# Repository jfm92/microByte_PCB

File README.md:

This repository contains the schematics and the PCB design of the microByte project with **KiCad 5.1.6.**

The 3D model of the components were obtained from [SnapEDA](https://www.snapeda.com/).

**If you want to know more about the microByte project go to the next link:**
[Github microByte](https://github.com/jfm92/microByte)

## 3D PCB Images

### PCB Front View

### PCB Bottom View

Note: Some of the compenent 3D models weren't available, thats the reason why they don't appear on the PCB.

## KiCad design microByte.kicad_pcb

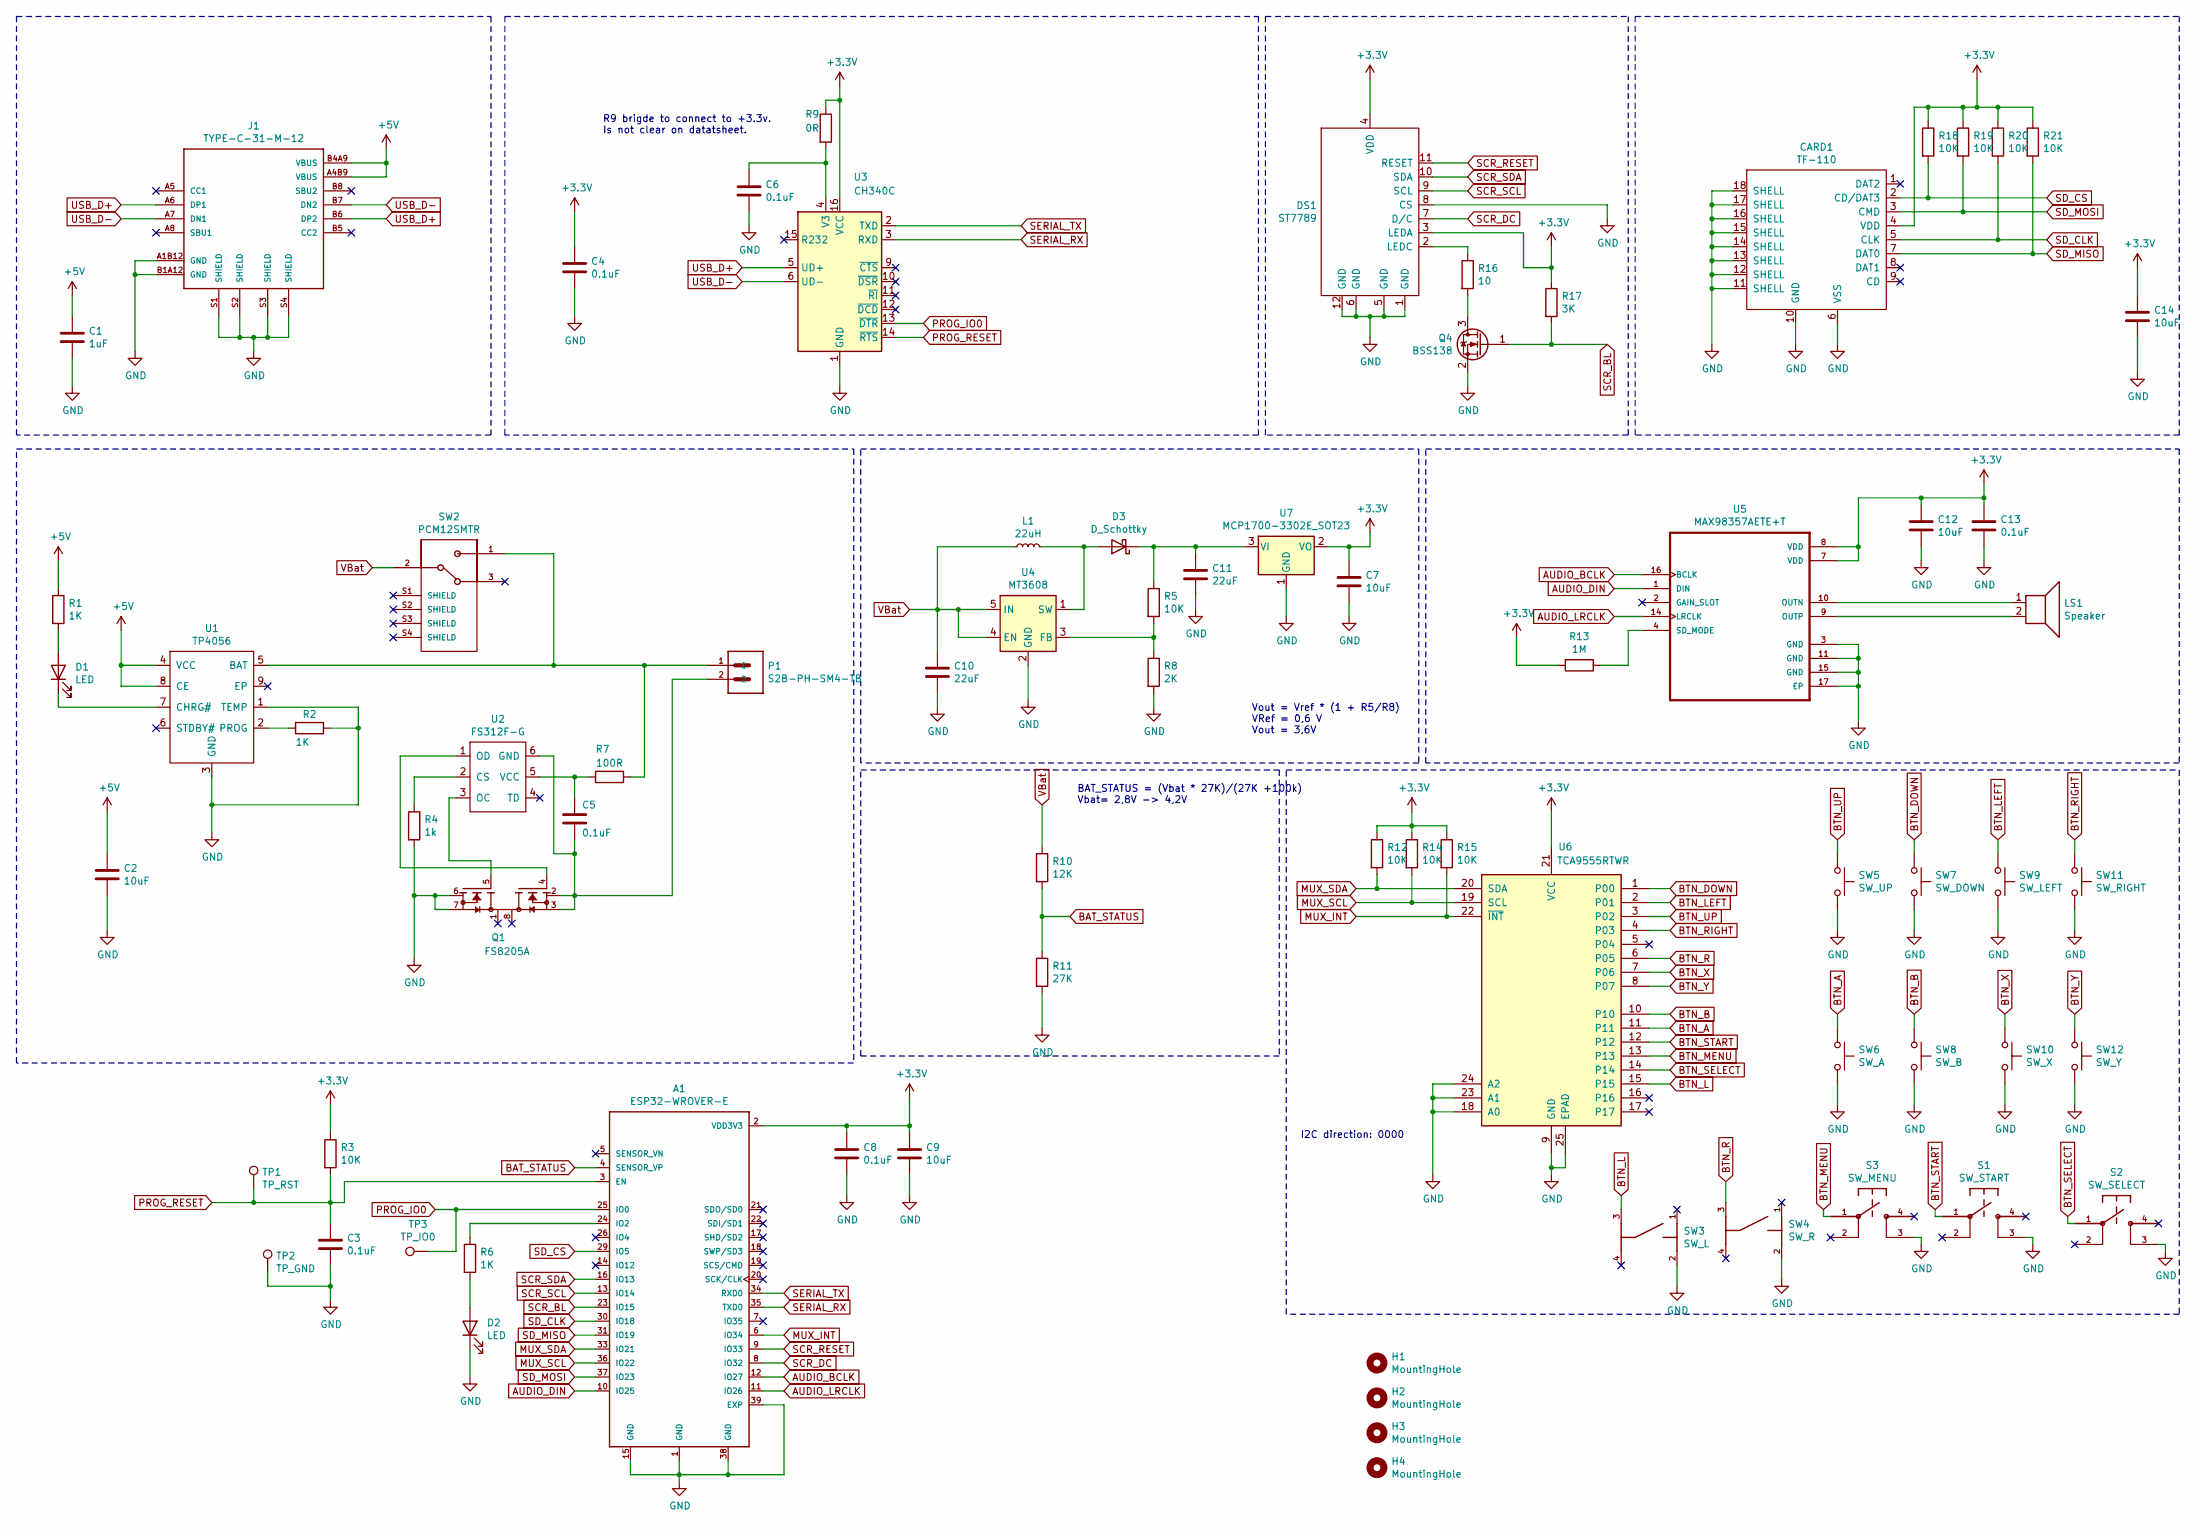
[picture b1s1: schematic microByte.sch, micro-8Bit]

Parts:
A1: ESP32-WROVER-E; XCVR_ESP32-WROVER-I
C1: 1uF; C_0805_2012Metric_Pad1.15x1.40mm_HandSolder
C2, C9, C12, C14: 10uF; C_0805_2012Metric_Pad1.15x1.40mm_HandSolder
C3, C4, C5, C6, C8, C13: 0.1uF; C_0603_1608Metric_Pad1.05x0.95mm_HandSolder
C7: 10uF; C_0805_2012Metric
C10, C11: 22uF; C_0805_2012Metric_Pad1.15x1.40mm_HandSolder
CARD1: TF-110
D1, D2: LED; LED_0805_2012Metric_Pad1.15x1.40mm_HandSolder
D3: D_Schottky; D_SMA_Handsoldering
DS1: ST7789
H1, H2, H3, H4: MountingHole; MountingHole_2.5mm
J1: TYPE-C-31-M-12; HRO_TYPE-C-31-M-12
L1: 22uH; Sunlord_SPH4012H220MT
LS1: Speaker; KLJ-5030
P1: S2B-PH-SM4-TB; JST_S2B-PH-SM4-TB
Q1: FS8205A; SOP65P640X120-8N
Q4: BSS138; SOT-23
R1, R2, R6: 1K; R_0805_2012Metric_Pad1.15x1.40mm_HandSolder
R3, R5, R12, R14, R15, R18, R19, R20, R21: 10K; R_0805_2012Metric_Pad1.15x1.40mm_HandSolder
R4: 1k; R_0805_2012Metric_Pad1.15x1.40mm_HandSolder
R7: 100R; R_0805_2012Metric_Pad1.15x1.40mm_HandSolder
R8: 2K; R_0805_2012Metric_Pad1.15x1.40mm_HandSolder
R9: 0R; R_0603_1608Metric_Pad1.05x0.95mm_HandSolder
R10: 12K; R_0805_2012Metric_Pad1.15x1.40mm_HandSolder
R11: 27K; R_0805_2012Metric_Pad1.15x1.40mm_HandSolder
R13: 1M; R_0805_2012Metric_Pad1.15x1.40mm_HandSolder
R16: 10; R_0805_2012Metric_Pad1.15x1.40mm_HandSolder
R17: 3K; R_0805_2012Metric_Pad1.15x1.40mm_HandSolder
S1: SW_START; TL3315NF100Q
S2: SW_SELECT; TL3315NF100Q
S3: SW_MENU; TL3315NF100Q
SW2: PCM12SMTR; SW_PCM12SMTR
SW3: SW_L; SW_434331013822
SW4: SW_R; SW_434331013822
SW5: SW_UP; BUTTON-CONDUCTIVE
SW6: SW_A; BUTTON-CONDUCTIVE
SW7: SW_DOWN; BUTTON-CONDUCTIVE
SW8: SW_B; BUTTON-CONDUCTIVE
SW9: SW_LEFT; BUTTON-CONDUCTIVE
SW10: SW_X; BUTTON-CONDUCTIVE
SW11: SW_RIGHT; BUTTON-CONDUCTIVE
SW12: SW_Y; BUTTON-CONDUCTIVE
TP1: TP_RST; TestPoint_Pad_D1.5mm
TP2: TP_GND; TestPoint_Pad_D1.5mm
TP3: TP_IO0; TestPoint_Pad_D1.5mm
U1: TP4056
U2: FS312F-G; SOT-23-6_Handsoldering
U3: CH340C; SOIC-16_3.9x9.9mm_P1.27mm
U4: MT3608; SOT-23-6
U5: MAX98357AETE+T; QFN50P300X300X80-17N
U6: TCA9555RTWR
U7: MCP1700-3302E_SOT23; SOT-23

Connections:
+3V3: A1.2 (VDD3V3), C4.1, C7.1, C8.1, C9.1, C12.1, C13.1, C14.1, CARD1.4 (VDD), DS1.3 (LEDA), DS1.4 (VDD), R3.1, R9.1, R12.1, R13.2, R14.1, R15.1, R17.1, R18.1, R19.1, R20.1, R21.1, U3.16 (VCC), U5.7 (VDD), U5.8 (VDD), U6.21 (VCC), U7.2 (VO)
+5V: C1.1, C2.1, J1.A4B9 (VBUS), J1.B4A9 (VBUS), R1.1, U1.4 (VCC), U1.8 (CE)
AUDIO_BCLK: A1.12 (IO27), U5.16 (BCLK)
AUDIO_DIN: A1.10 (IO25), U5.1 (DIN)
AUDIO_LRCLK: A1.11 (IO26), U5.14 (LRCLK)
BAT_STATUS: A1.4 (SENSOR_VP), R10.2, R11.1
BTN_A: SW6.1, U6.11
BTN_B: SW8.1, U6.10
BTN_DOWN: SW7.1, U6.1 (P00)
BTN_L: SW3.3, U6.15
BTN_LEFT: SW9.1, U6.2 (P01)
BTN_MENU: S3.1, U6.13
BTN_R: SW4.3, U6.6 (P05)
BTN_RIGHT: SW11.1, U6.4 (P03)
BTN_SELECT: S2.1, U6.14
BTN_START: S1.1, U6.12
BTN_UP: SW5.1, U6.3 (P02)
BTN_X: SW10.1, U6.7 (P06)
BTN_Y: SW12.1, U6.8 (P07)
GND: A1.1 (GND), A1.15 (GND), A1.38 (GND), A1.39 (EXP), C1.2, C2.2, C3.2, C4.2, C6.2, C7.2, C8.2, C9.2, C10.2, C11.2, C12.2, C13.2, C14.2, CARD1.6 (VSS), CARD1.10 (GND), CARD1.11 (SHELL), CARD1.12 (SHELL), CARD1.13 (SHELL), CARD1.14 (SHELL), CARD1.15 (SHELL), CARD1.16 (SHELL), CARD1.17 (SHELL), CARD1.18 (SHELL), D2.1 (K), DS1.1 (GND), DS1.5 (GND), DS1.6 (GND), DS1.8 (CS), DS1.12 (GND), J1.A1B12 (GND), J1.B1A12 (GND), J1.S1 (SHIELD), J1.S2 (SHIELD), J1.S3 (SHIELD), J1.S4 (SHIELD), Q1.6, Q1.7, Q4.2 (S), R2.1, R4.2, R8.2, R11.2, S1.3, S2.3, S3.3, SW3.2, SW4.2, SW5.2, SW6.2, SW7.2, SW8.2, SW9.2, SW10.2, SW11.2, SW12.2, TP2.1, U1.1 (TEMP), U1.3 (GND), U3.1 (GND), U4.2 (GND), U5.3 (GND), U5.11 (GND), U5.15 (GND), U5.17 (EP), U6.9 (GND), U6.18 (A0), U6.23 (A1), U6.24 (A2), U6.25 (EPAD), U7.1 (GND)
MUX_INT: A1.6 (IO34), R15.2, U6.22 (~INT)
MUX_SCL: A1.36 (IO22), R14.2, U6.19 (SCL)
MUX_SDA: A1.33 (IO21), R12.2, U6.20 (SDA)
unnamed: A1.24 (IO2), R6.1
unnamed: C5.1, R7.1, U2.5 (VCC)
unnamed: C5.2, P1.2, Q1.2, Q1.3, U2.6 (GND)
unnamed: C6.1, R9.2, U3.4 (V3)
unnamed: C11.1, D3.1 (K), R5.1, U7.3 (VI)
unnamed: D1.1 (K), U1.7 (CHRG#)
unnamed: D1.2 (A), R1.2
unnamed: D2.2 (A), R6.2
unnamed: D3.2 (A), L1.2, U4.1 (SW)
unnamed: DS1.2 (LEDC), R16.1
unnamed: LS1.1, U5.10 (OUTN)
unnamed: LS1.2, U5.9 (OUTP)
unnamed: P1.1, R7.2, SW2.1, U1.5 (BAT)
unnamed: Q1.4, U2.1 (OD)
unnamed: Q1.5, U2.3 (OC)
unnamed: Q4.3 (D), R16.2
unnamed: R2.2, U1.2 (PROG)
unnamed: R4.1, U2.2 (CS)
unnamed: R5.2, R8.1, U4.3 (FB)
unnamed: R13.1, U5.4 (SD_MODE)
PROG_IO0: A1.25 (IO0), TP3.1, U3.13 (~DTR)
PROG_RESET: A1.3 (EN), C3.1, R3.2, TP1.1, U3.14 (~RTS)
SCR_BL: A1.23 (IO15), Q4.1 (G), R17.2
SCR_DC: A1.8 (IO32), DS1.7 (D/C)
SCR_RESET: A1.9 (IO33), DS1.11 (RESET)
SCR_SCL: A1.13 (IO14), DS1.9 (SCL)
SCR_SDA: A1.16 (IO13), DS1.10 (SDA)
SD_CLK: A1.30 (IO18), CARD1.5 (CLK), R20.2
SD_CS: A1.29 (IO5), CARD1.2 (CD/DAT3), R18.2
SD_MISO: A1.31 (IO19), CARD1.7 (DAT0), R21.2
SD_MOSI: A1.37 (IO23), CARD1.3 (CMD), R19.2
SERIAL_RX: A1.35 (TXD0), U3.3 (RXD)
SERIAL_TX: A1.34 (RXD0), U3.2 (TXD)
USB_D+: J1.A6 (DP1), J1.B6 (DP2), U3.5 (UD+)
USB_D-: J1.A7 (DN1), J1.B7 (DN2), U3.6 (UD-)
VBat: C10.1, L1.1, R10.1, SW2.2, U4.4 (EN), U4.5 (IN)

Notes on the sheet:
I2C direction: 0000
R9 brigde to connect to +3.3v. Is not clear on datatsheet.
Vout = Vref * (1 + R5/R8) VRef = 0,6 V Vout = 3,6V
BAT_STATUS = (Vbat * 27K)/(27K +100k) Vbat= 2,8V -> 4,2V

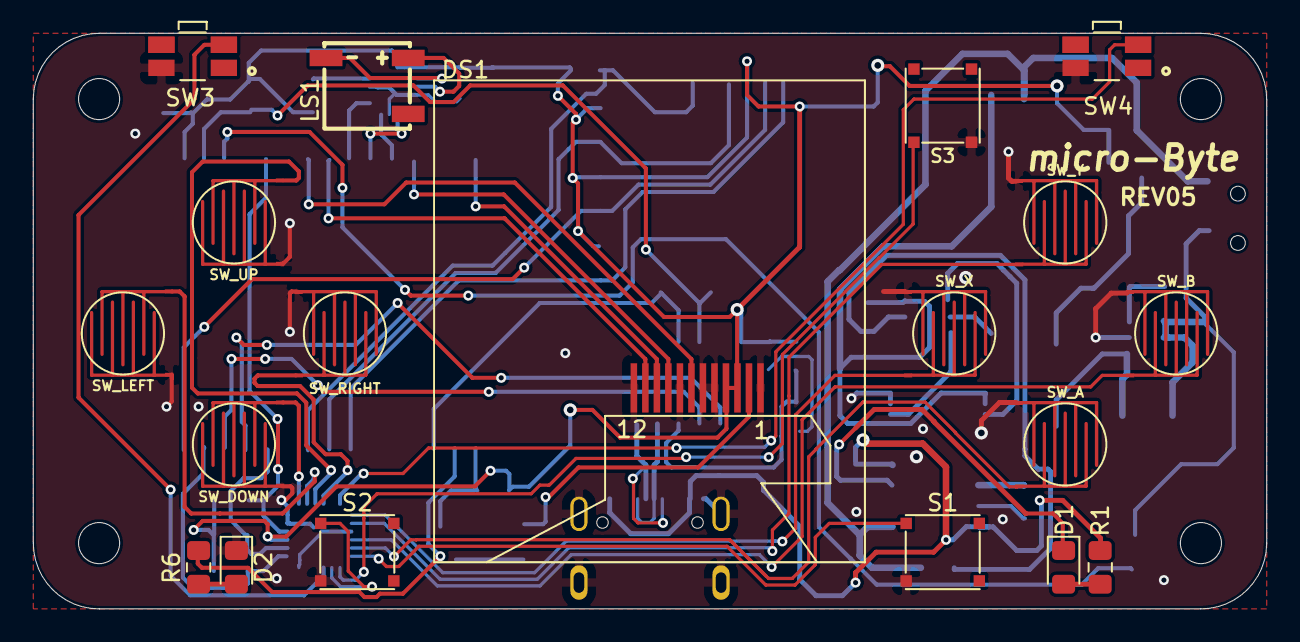
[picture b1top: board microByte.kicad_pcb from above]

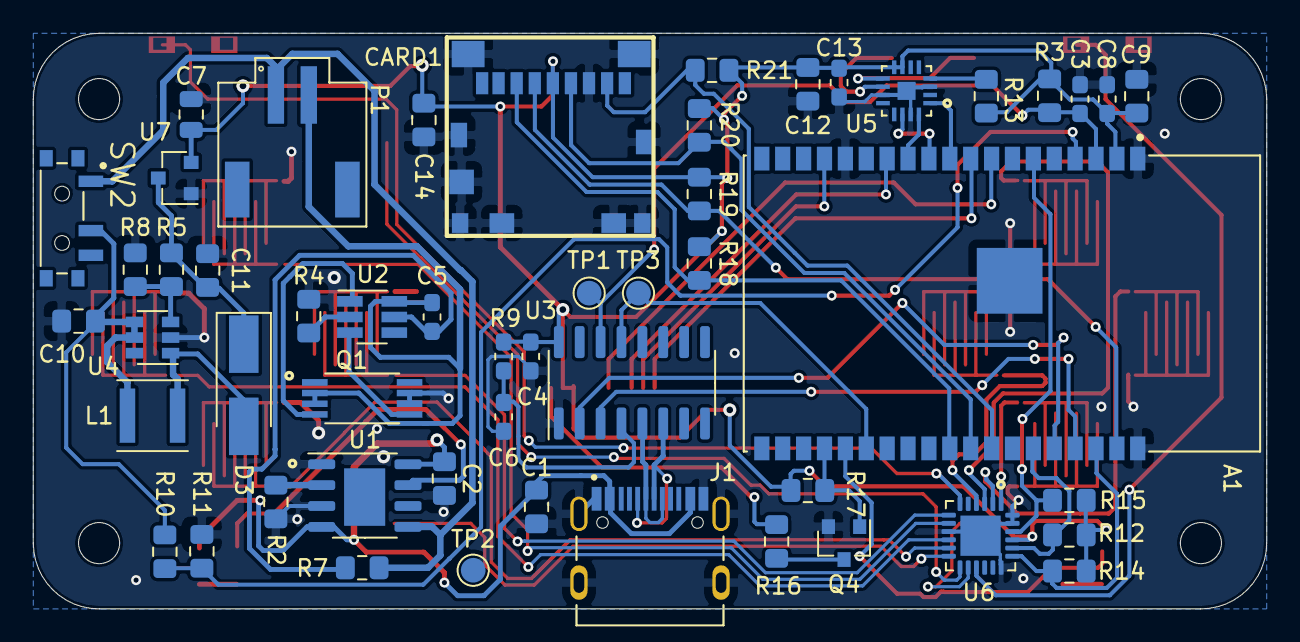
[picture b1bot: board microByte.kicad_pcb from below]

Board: 2 copper layers, 75.0 x 35.0 mm, 75 parts (52 on the bottom side), 59 nets.

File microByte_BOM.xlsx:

Reference | Quantity | Designatation | Package |  | Link
A1 | 1 | ESP32-WROVER-E (16MB ) | - |  | Espressif Systems|Espressif Systems ESP32-WROVER-E(16MB)|WIFI Modules|LCSC
C1 | 1 | 1uF | C_0805_2012Metric
C11 C10 | 2 | 22uF | C_0805_2012Metric
C12 C14 C9 C2 | 4 | 10uF | C_0805_2012Metric
C13 C8 C3 C5 C6 C4 | 6 | 0.1uF | C_0603_1608Metric
C7 | 1 | 10uF | C_0805_2012Metric
CARD1 | 1 | TF-110 | -
D1 D2 | 2 | LED | LED_0805_2012Metric
D3 | 1 | D_Schottky | D_SMA
DS1 | 1 | ST7789 1.3" | -
H1 H2 H3 H4 | 4 | MountingHole | -
J1 | 1 | TYPE-C-31-M-12 | -
L1 | 1 | 22uH | -
LS1 | 1 | Speaker | - |  | KELIKING|KELIKING KLJ-5030|Buzzers|LCSC
P1 | 1 | S2B-PH-SM4-TB | - |  | Ckmtw(Shenzhen Cankemeng)|Ckmtw(Shenzhen Cankemeng) C132500|Wire To Board / Wir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
Q1 | 1 | FS8205A | SOP65P640X120-8N |  | Fortune Semicon|Fortune Semicon FS8205A|MOSFET|LCSC
Q4 | 1 | BSS138 | SOT-23
R1 R6 R2 | 3 | 1K | R_0805_2012Metric
R10 | 1 | 12K | R_0805_2012Metric
R11 | 1 | 27K | R_0805_2012Metric
R13 | 1 | 1M | R_0805_2012Metric
R16 | 1 | 10R | R_0805_2012Metric
R17 | 1 | 3K | R_0805_2012Metric
R18 R19 R20 R21 R12 R14 R15 R3 R5 | 9 | 10K | R_0805_2012Metric
R4 | 1 | 1k | R_0805_2012Metric
R7 | 1 | 100R | R_0805_2012Metric
R8 | 1 | 2K | R_0805_2012Metric
R9 | 1 | 0R | R_0805_2012Metric
S1 | 1 | SW_START | -
S2 | 1 | SW_SELECT | -
S3 | 1 | SW_MENU | -
SW10 | 1 | SW_X | -
SW11 | 1 | SW_RIGHT | -
SW12 | 1 | SW_Y | -
SW2 | 1 | PCM12SMTR | - |  | Korean Hroparts Elec|Korean Hroparts Elec K3-1296S-E2|Toggle Switches|LCSC
SW3 | 1 | SW_L | - |  | ALPSALPINE|ALPSALPINE SKSCLCE010|Tactile Switches|LCSC
SW4 | 1 | SW_R | - |  | ALPSALPINE|ALPSALPINE SKSCLCE010|Tactile Switches|LCSC
SW5 | 1 | SW_UP | -
SW6 | 1 | SW_A | -
SW7 | 1 | SW_DOWN | -
SW8 | 1 | SW_B | -
SW9 | 1 | SW_LEFT | -
TP1 | 1 | TP_RST | -
TP2 | 1 | TP_GND | -
TP3 | 1 | TP_IO0 | -
U1 | 1 | TP4056 | ESOP8 |  | TOPPOWER(Nanjing Extension Microelectronics)|TOPPOWER(Nanjing Extension Microel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
U2 | 1 | FS312F-G | SOT-23-6 |  | Fortune Semicon|Fortune Semicon FS312F-G|Battery Protection ICs|LCSC
U3 | 1 | CH340C | SOIC-16 |  | WCH(Jiangsu Qin Heng)|WCH(Jiangsu Qin Heng) CH340C|USB ICs|LCSC
U4 | 1 | MT3608 | SOT-23-6 |  | XI'AN Aerosemi Tech|XI'AN Aerosemi Tech MT3608|DC-DC Converters|LCSC
U5 | 1 | MAX98357AETE+T | TQFN
U6 | 1 | TCA9555RTWR | 24-Pin WQFN
U7 | 1 | MCP1700-3302E_SOT23 | SOT-23

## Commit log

2020-11-25 microByte_PCB v1.5
2020-11-25 Readme fix
2020-11-25 Update bottom image
2021-02-05 Addind BOM with links to strange components

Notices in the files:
microByte.sch:
creativecommons.org/licenses/by/4.0
License: CC by 4.0
